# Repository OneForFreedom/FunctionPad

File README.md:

# FunctionPad
If I make a 60% iso keyboard, how am I gonna use function keys? This is legit just 12 keys from f1-12.

## EYE CANDY!

## PCB
  
## SCHEMATIC

## Bill of Materials (BOM)

| Item            | Quantity |
|-----------------|----------|
| Keycap-Black    | 12       |
| XIAO-RP2040     | 1        |
| Switches        | 12       |
| 1N4148 DIODE    | 12       |

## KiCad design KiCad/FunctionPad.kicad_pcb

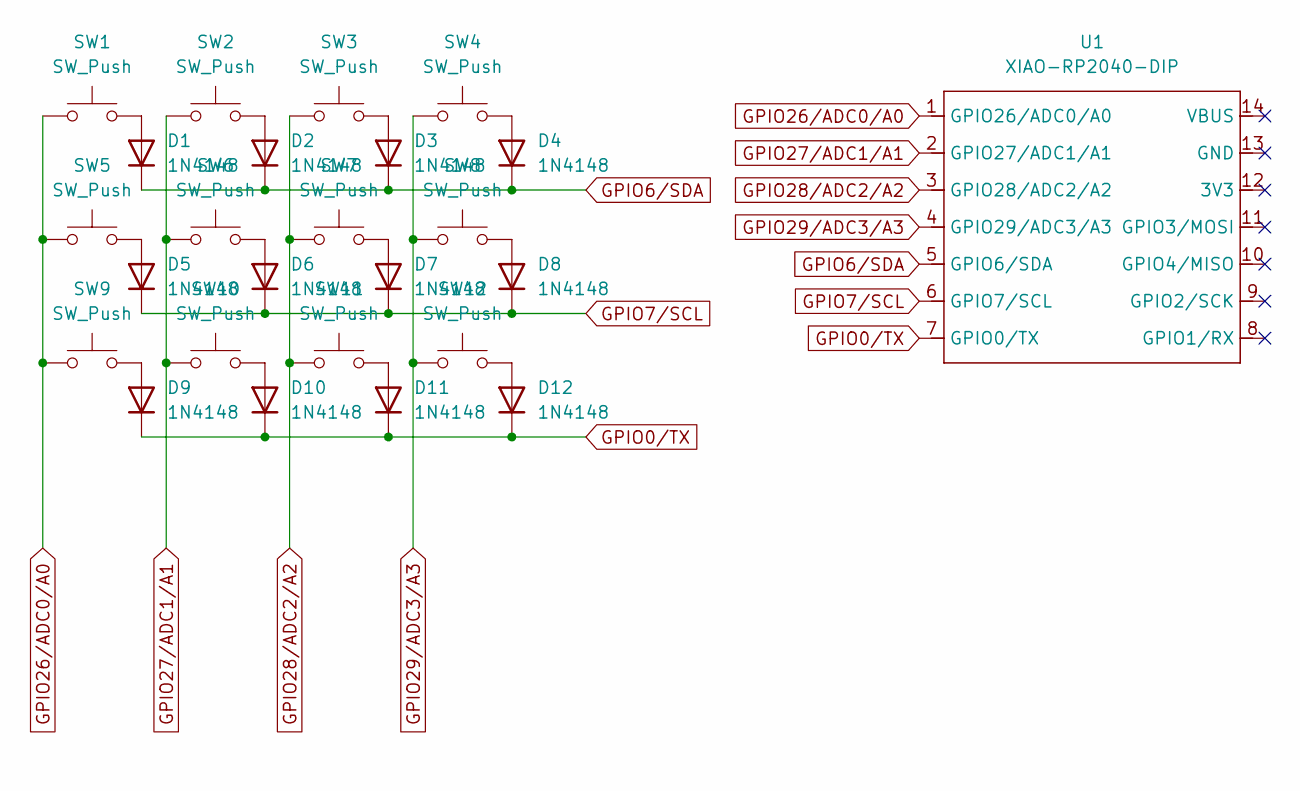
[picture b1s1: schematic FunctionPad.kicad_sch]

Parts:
D1, D2, D3, D4, D5, D6, D7, D8, D9, D10, D11, D12: 1N4148; D_DO-35_SOD27_P7.62mm_Horizontal
SW1, SW2, SW3, SW4, SW5, SW6, SW7, SW8, SW9, SW10, SW11, SW12: SW_Push; SW_Cherry_MX_1.00u_PCB WITH 3D
U1: XIAO-RP2040-DIP

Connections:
GPIO0/TX: D9.1 (K), D10.1 (K), D11.1 (K), D12.1 (K), U1.7 (GPIO0/TX)
GPIO6/SDA: D1.1 (K), D2.1 (K), D3.1 (K), D4.1 (K), U1.5 (GPIO6/SDA)
GPIO7/SCL: D5.1 (K), D6.1 (K), D7.1 (K), D8.1 (K), U1.6 (GPIO7/SCL)
GPIO26/ADC0/A0: SW1.1, SW5.1, SW9.1, U1.1 (GPIO26/ADC0/A0)
GPIO27/ADC1/A1: SW2.1, SW6.1, SW10.1, U1.2 (GPIO27/ADC1/A1)
GPIO28/ADC2/A2: SW3.1, SW7.1, SW11.1, U1.3 (GPIO28/ADC2/A2)
GPIO29/ADC3/A3: SW4.1, SW8.1, SW12.1, U1.4 (GPIO29/ADC3/A3)
unnamed: D1.2 (A), SW1.2
unnamed: D2.2 (A), SW2.2
unnamed: D3.2 (A), SW3.2
unnamed: D4.2 (A), SW4.2
unnamed: D5.2 (A), SW5.2
unnamed: D6.2 (A), SW6.2
unnamed: D7.2 (A), SW7.2
unnamed: D8.2 (A), SW8.2
unnamed: D9.2 (A), SW9.2
unnamed: D10.2 (A), SW10.2
unnamed: D11.2 (A), SW11.2
unnamed: D12.2 (A), SW12.2

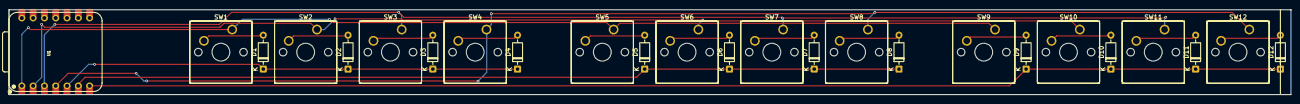
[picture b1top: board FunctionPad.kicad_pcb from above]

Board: 2 copper layers, 288.1 x 19.0 mm, 25 parts (0 on the bottom side), 19 nets.

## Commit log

2025-08-28 Rename FunctionPad.zip to Production/FunctionPad.zip
2025-08-28 Rename FusionPad PCB.step to FunctionPad PCB.step
2025-08-28 Rename FunctionPad.kicad_pro to KiCad/FunctionPad.kicad_pro
2025-08-28 Rename Screenshot 2025-08-28 110827.png to Images/Screenshot 2025-08-28 110827.png
2025-08-28 Rename Code.ino to Code/Code.ino
